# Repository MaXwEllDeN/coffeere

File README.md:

# Coffeere

## Overview

Coffeere is a platform for those of you who got tired of going to the kitchen just to realize that the coffee bottle is empty :tired_face:.

## Requirements

* [HX711 Weight Load library](https://github.com/bogde/HX711)
* [ESP8266 FS Tool](https://github.com/esp8266/arduino-esp8266fs-plugin)
* [ArduinoJson library version 6.12.0](https://github.com/bblanchon/ArduinoJson)

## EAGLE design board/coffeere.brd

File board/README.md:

# Coffeere

## Board

This directory contains the [Autodesk's EAGLE](https://www.autodesk.com/products/eagle/overview) project files needed to produce the board.

## Printed Circuit Board

### Board after the layout transference

### Board with ESP8266-12e soldered

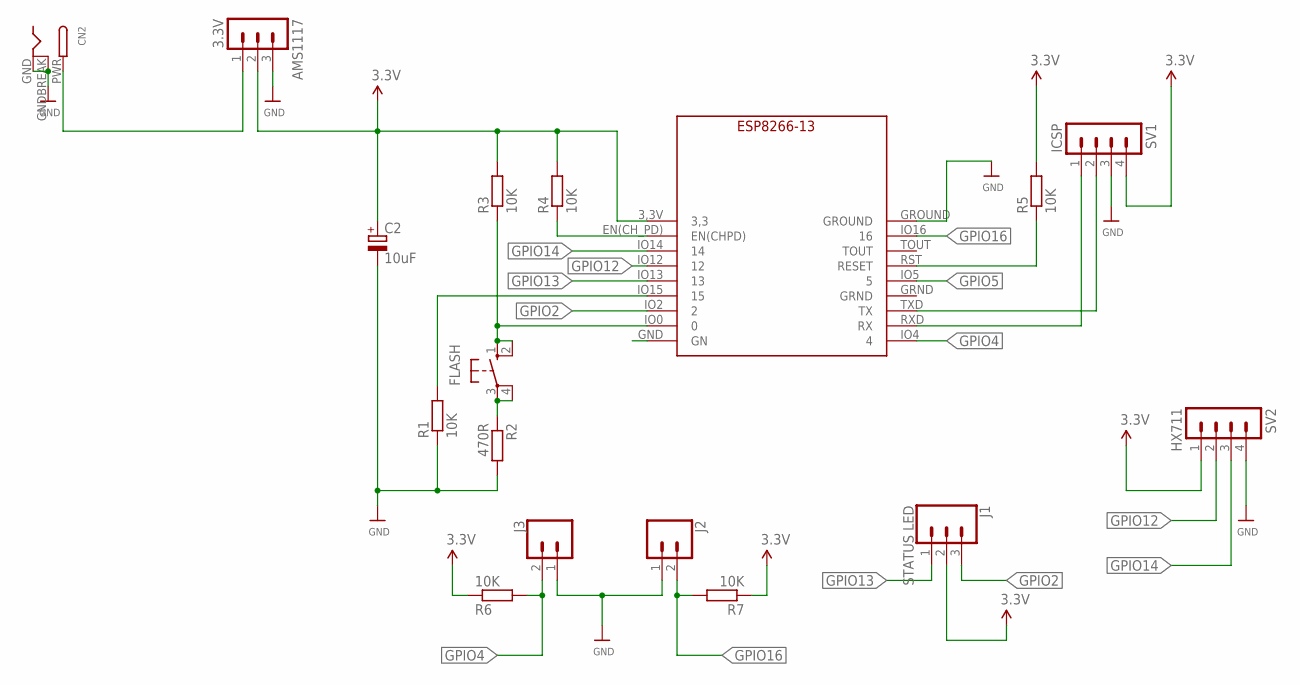
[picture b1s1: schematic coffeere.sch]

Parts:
AMS1117: 3.3V; MA03-1
C2: 10uF; E2,5-6
CN2: DCBARRELPTH; DCJACK_2MM_PTH
FLASH: 10-XX; B3F-10XX
J1: STATUS LED; 1X03
J2, J3: CONN_02; 1X02
R1, R3, R4, R5, R6, R7: 10K; 0207/10
R2: 470R; 0207/10
SV1: ICSP; MA04-1
SV2: HX711; MA04-1
U$1: ESP8266-13

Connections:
3.3V: AMS1117.2, C2.+, J1.2, R3.2, R4.2, R5.2, R6.1, R7.1, SV1.4, SV2.1, U$1.3,3V (3,3)
GND: AMS1117.3, C2.-, CN2.GND, CN2.GNDBREAK, J2.1, J3.1, R1.1, R2.2, SV1.3, SV2.4, U$1.GROUND
GPIO0: FLASH.1 (S), FLASH.2 (S1), R3.1, U$1.IO0 (0)
GPIO2: J1.3, U$1.IO2 (2)
GPIO4: J3.2, R6.2, U$1.IO4 (4)
GPIO5: U$1.IO5 (5)
GPIO12: SV2.2, U$1.IO12 (12)
GPIO13: J1.1, U$1.IO13 (13)
GPIO14: SV2.3, U$1.IO14 (14)
GPIO15: R1.2, U$1.IO15 (15)
GPIO16: J2.2, R7.2, U$1.IO16 (16)
unnamed: AMS1117.1, CN2.PWR
unnamed: SV1.2, U$1.TXD (TX)
unnamed: SV1.1, U$1.RXD (RX)
unnamed: FLASH.3, FLASH.4 (P1), R2.1
unnamed: R5.1, U$1.RST (RESET)
unnamed: R4.1, U$1.EN(CH_PD) (EN(CHPD))

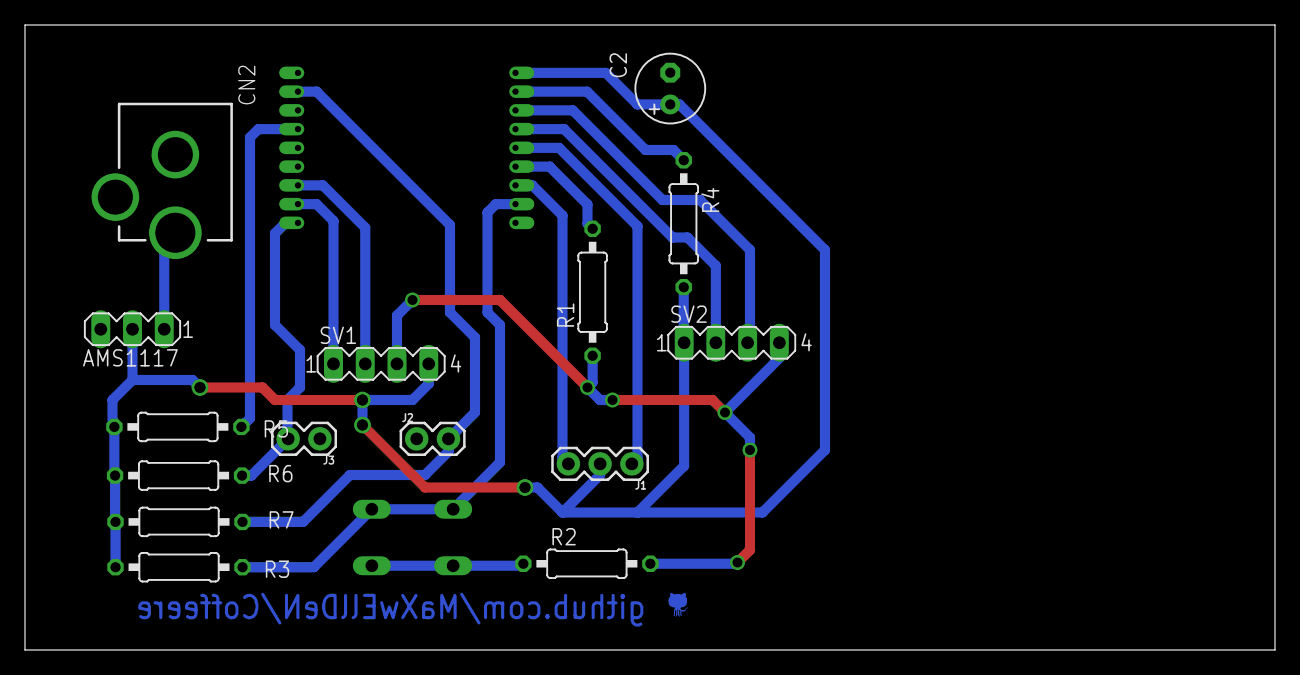
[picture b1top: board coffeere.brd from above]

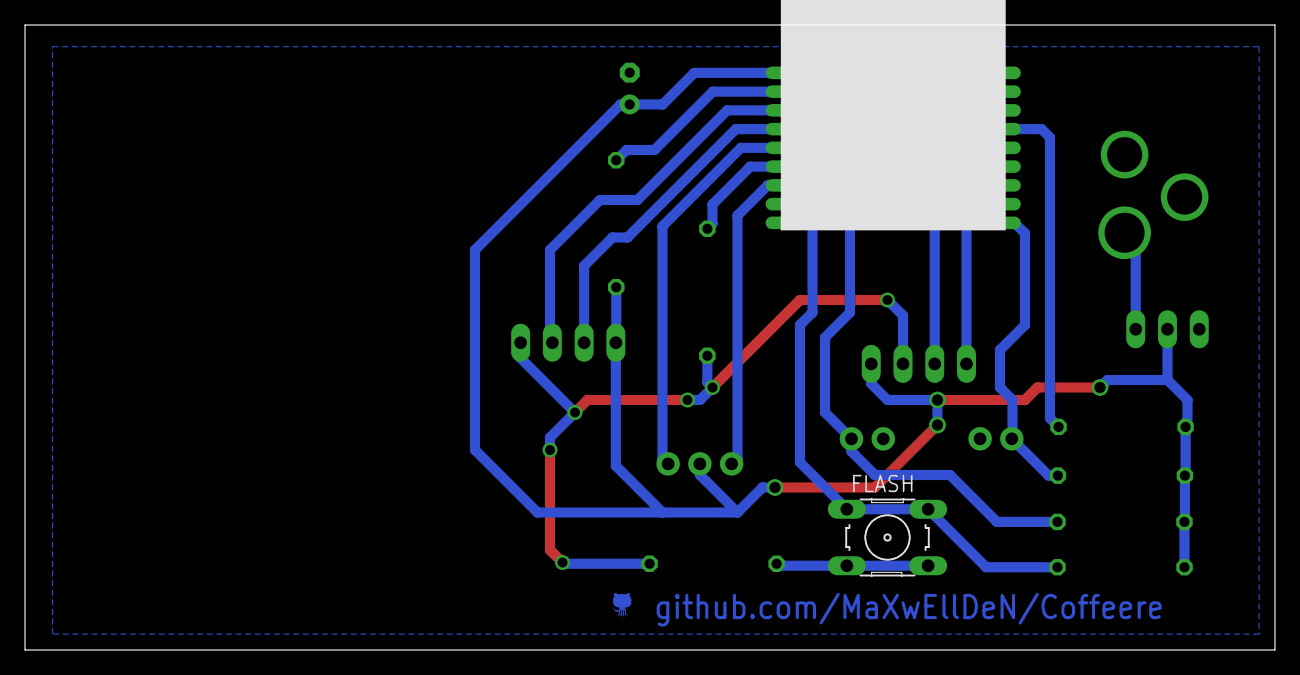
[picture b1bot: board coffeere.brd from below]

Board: 2 copper layers, 100.0 x 50.0 mm, 17 parts (2 on the bottom side), 16 nets.

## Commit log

2019-07-07 Uploading project files.
2019-07-07 Adding Remote Server Flask App.
2019-07-08 Adding Dependencies.
2019-07-12 Fixing isAppletConfigured issue.
2019-07-12 Adding clausure to ignore Eagle's schematic backup files.
2019-07-12 Uploading .gitignore.
2019-07-13 Updating button handler.
2019-07-21 Changing pinout to better suit the board design.
2019-07-21 Creating schemetic and board designs.
2019-07-21 Renaming coffere.ino -> esp8266.ino due to Arduino requirement.
2019-07-21 Changing folders structure.
2019-10-04 Fixing board issues
2019-10-08 Update README.md
    Adding ArduinoJson library as requirement.
2019-10-08 Using nginx to serve a static webserver for the client application.
2019-10-08 Updating board's directory README.md.
2019-12-13 Migrando para um servidor Flask e adicionando push notifications.
2019-12-16 Removing flask client.
2019-12-16 Adding flask client.
2019-12-16 Creating subscription persistance through sqlite database.

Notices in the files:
README.md:
License: Apache 2.0
parts and their libraries:
SparkFun-Connectors: Licensing: Creative Commons ShareAlike 4.0 International - https://creativecommons.org/licenses/by-sa/4.0
microbuilder: This work is placed in the public domain, and may be freely used for commercial and non-commercial work with the following conditions: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
